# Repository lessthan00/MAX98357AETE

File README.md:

# MAX98357AETE  

[音频功率放大器](https://www.jlc-smt.com/lcsc/detail?componentCode=C910544)  
  
D级运放  
  
重点  
SD_MODE# 下拉到地关断, (I2S LJmode)-> data channel  
(TDM mode)-> SD_MODE# & GAIN_SLOT -> channel selection  
  
SD_MODE STATUS                                      SELECTED CHANNEL  
VSD_MODE > B2 trip point(1.4V)                    Left  
B2 trip point > VSD_MODE > B1 trip point(0.77V)    Right  
B1 trip point > VSD_MODE > B0 trip point(0.16V)    (Left/2 + right/2)  
B0 trip point > VSD_MODE                            Shutdown  

Vref * RL / (RH + RL) = Vo  
RH = (Vref * RL / Vo) - RL  
当RL = 100K, Vref = 3.3V  
(3.3 + 1.4)/2 = 2.35 => 40K (这个直接接VDD而不是40K)  
(1.4 + 0.77)/2 = 1.085 => 204K  
(0.77 + 0.16)/2 = 0.465 => 609K  

GAIN_SLOT  
GND GND(100K) float VDD(100K) VDD  
  
GAIN_SLOT    I2S/LJ GAIN (dB)  
GND(100K) 15dB  
GND         12dB  
flaot       9  
VDD         6  
VDD(100K)   3  
  
I2S Digital Audio Interface  
LRCLK  
BCLK  
DIN  
  
最大的问题是封装, 感觉有点小,焊接会比较困难.不如直接买模块,当然也可以尝试以下.

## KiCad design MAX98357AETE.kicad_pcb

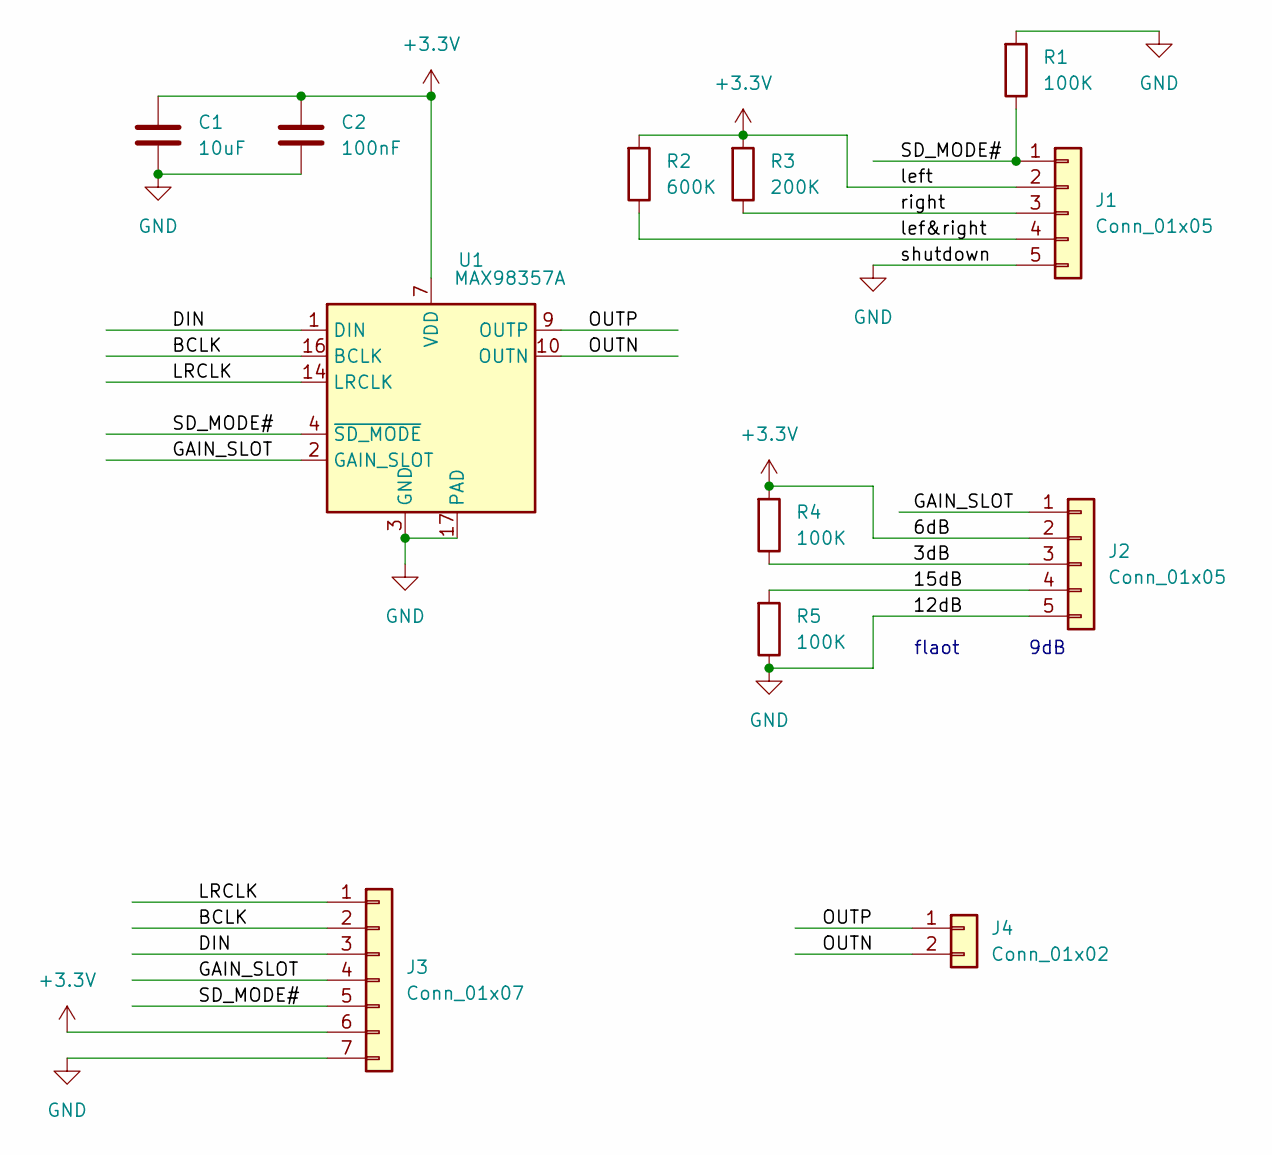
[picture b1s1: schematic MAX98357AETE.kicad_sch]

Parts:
C1: 10uF; C_1206_3216Metric
C2: 100nF; C_1206_3216Metric
J1, J2: Conn_01x05; PinHeader_1x03_P2.54mm_Vertical
J3: Conn_01x07; PinHeader_1x07_P2.54mm_Vertical
J4: Conn_01x02; TerminalBlock_Phoenix_MKDS-1,5-2-5.08_1x02_P5.08mm_Horizont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
R1, R4, R5: 100K; R_1206_3216Metric
R2: 600K; R_1206_3216Metric
R3: 200K; R_1206_3216Metric
U1: MAX98357A; TQFN-16-1EP_3x3mm_P0.5mm_EP1.23x1.23mm

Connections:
+3.3V: C1.1, C2.1, J1.2, J2.2, J3.6, R2.1, R3.1, R4.1, U1.7 (VDD), U1.8 (VDD)
/3dB: J2.3, R4.2
/15dB: J2.4, R5.1
/BCLK: J3.2, U1.16 (BCLK)
/DIN: J3.3, U1.1 (DIN)
/GAIN_SLOT: J2.1, J3.4, U1.2 (GAIN_SLOT)
/LRCLK: J3.1, U1.14 (LRCLK)
/OUTN: J4.2, U1.10 (OUTN)
/OUTP: J4.1, U1.9 (OUTP)
/SD_MODE#: J1.1, J3.5, R1.2, U1.4 (~SD_MODE)
/lef&right: J1.4, R2.2
/right: J1.3, R3.2
GND: C1.2, C2.2, J1.5, J2.5, J3.7, R1.1, R5.2, U1.3 (GND), U1.11 (GND), U1.15 (GND), U1.17 (PAD)

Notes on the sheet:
flaot 9dB

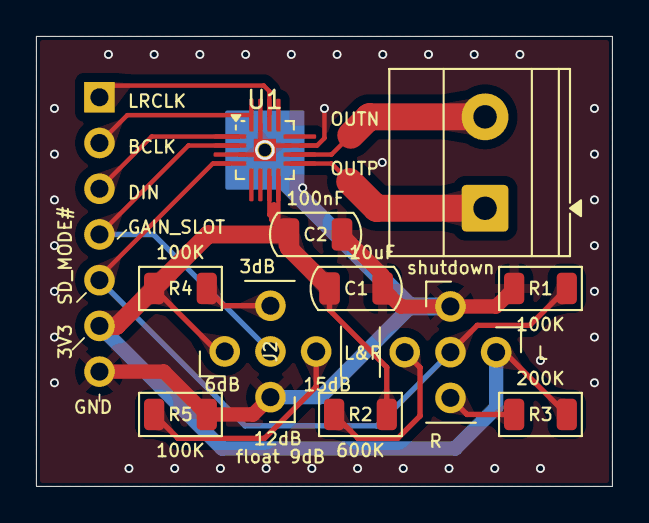
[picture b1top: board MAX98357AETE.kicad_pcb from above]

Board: 2 copper layers, 32.0 x 25.0 mm, 12 parts (1 on the bottom side), 13 nets.
